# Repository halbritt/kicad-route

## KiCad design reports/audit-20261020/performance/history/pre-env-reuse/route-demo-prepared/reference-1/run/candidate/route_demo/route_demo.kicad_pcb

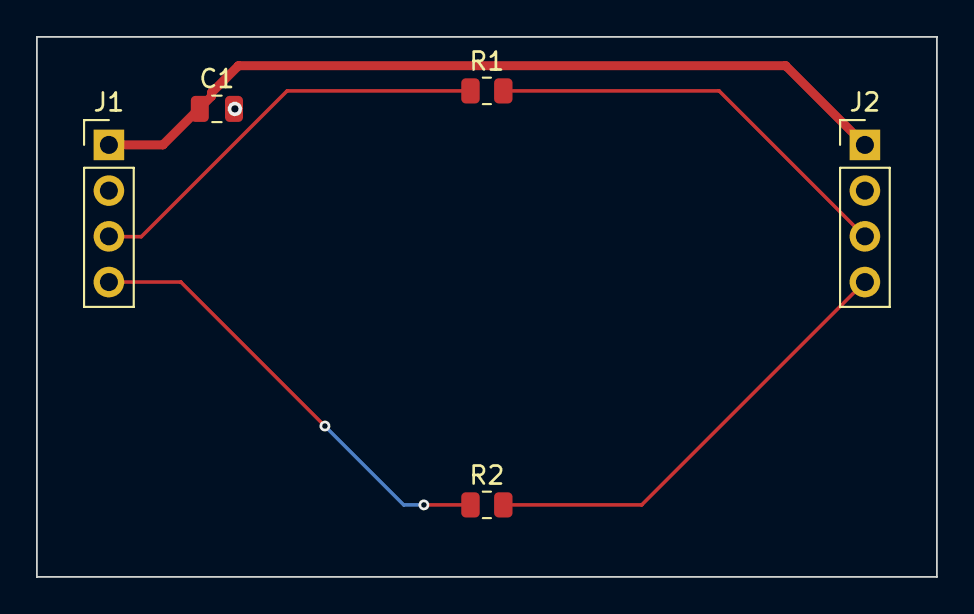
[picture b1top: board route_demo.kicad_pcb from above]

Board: 2 copper layers, 50.0 x 30.0 mm, 5 parts (0 on the bottom side), 6 nets.

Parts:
C1: 1u; C_0805_2012Metric
J1, J2: Conn_01x04; PinHeader_1x04_P2.54mm_Vertical
R1, R2: 33; R_0805_2012Metric

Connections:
/SIG_A: J1.3, R1.1
/SIG_A_OUT: J2.3, R1.2
/SIG_B: J1.4, R2.1
/SIG_B_OUT: J2.4, R2.2
/VIN: C1.1, J1.1, J2.1
GND: C1.2, J1.2, J2.2
